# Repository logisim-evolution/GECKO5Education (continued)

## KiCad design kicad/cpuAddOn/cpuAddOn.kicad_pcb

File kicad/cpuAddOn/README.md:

# GECKO5Education CPU-addon

This design can be used with the GECKO5Education or standalone and provides
an educational base for programming related classes.
In case this board is used with the GECKO5Education, the FTDI-chip is automatically
routed to the integrated USB-hub, meaning that you only require one USB-C connection. 
In case of this situation, the USB-C connector of the GECKO5Education is disabled, and all
functionality is provided by the USB-C connector of the CPU-addon board.

# Debugging

This board integrates a [Black Magic Probe](https://black-magic.org/index.html). After production
it needs to be programmed with the DFU-firmware once by an external programmer. After this firmware-
updates can be performed as with the normal Black Magic Probe.

# External connections

This boards integrates an extention connector (32 positions) that provides two 
[PMOD-compatible](https://digilent.com/reference/_media/reference/pmod/pmod-interface-specification-1_2_0.pdf)
interfaces. The different possibilities are listed below:

PMOD1:

|Pin|function1|function2|function3|
|:-:|:--------|:--------|:--------|
|1  |GPIO     |SPI6nCS  |I2S1_WS  |
|2  |GPIO     |SPI6MOSI |I2S1_SDO |
|3  |GPIO     |SPI6MISO |I2S1_SDI |
|4  |GPIO     |SPI6SCK  |I2S1_CK  |
|7  |GPIO     |EXTI5    |         |
|8  |GPIO     |EXTI6    |         |
|9  |GPIO     |SCL4     |         |
|10 |GPIO     |SDA4     |         |

PMOD2:

|Pin|function1|function2|function3|
|:-:|:--------|:--------|:--------|
|1  |GPIO     |CTS2     |         |
|2  |GPIO     |TX2      |         |
|3  |GPIO     |RX2      |         |
|4  |GPIO     |RTS2     |         |
|7  |GPIO     |EXTI13   |         |
|8  |GPIO     |ADC1_2_3 |EXTI0    |
|9  |GPIO     |ADC1_2_3 |EXTI1    |
|10 |GPIO     |ADC3     |EXTI10   |

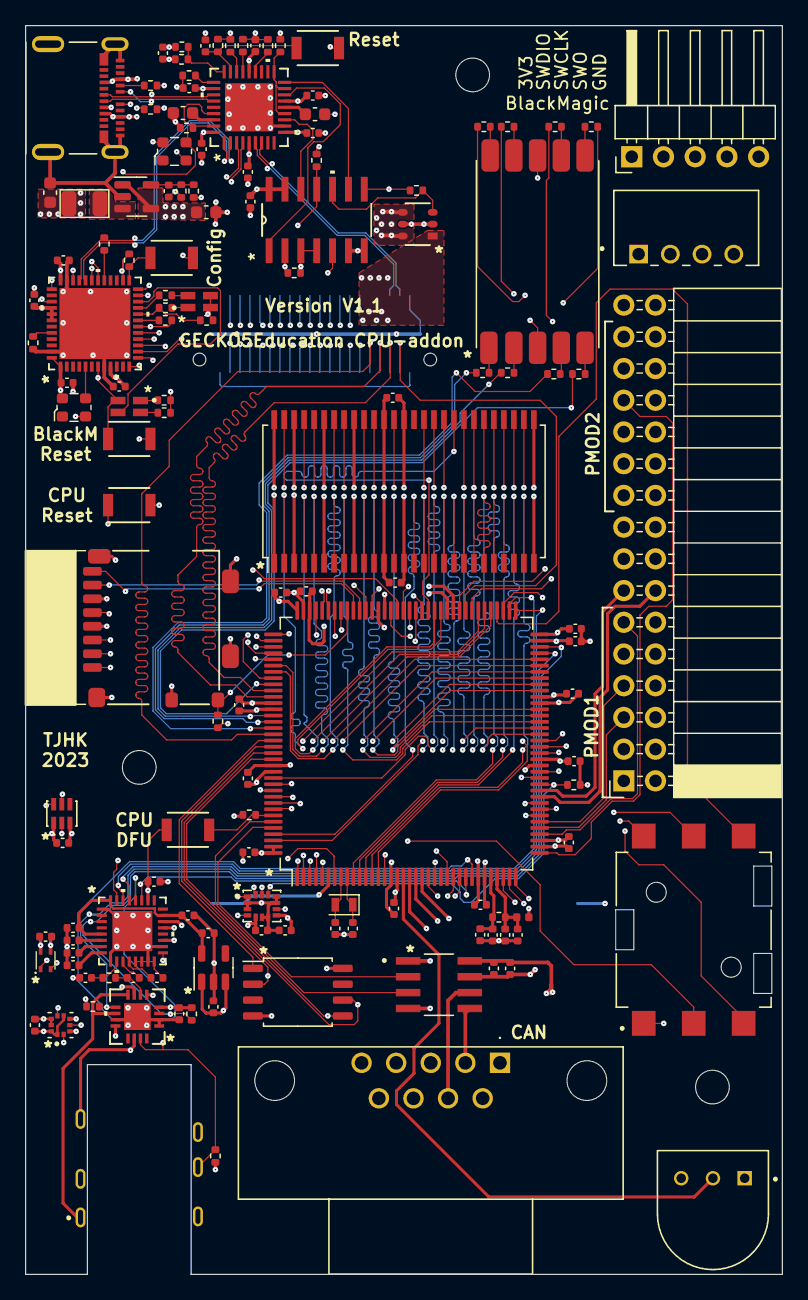
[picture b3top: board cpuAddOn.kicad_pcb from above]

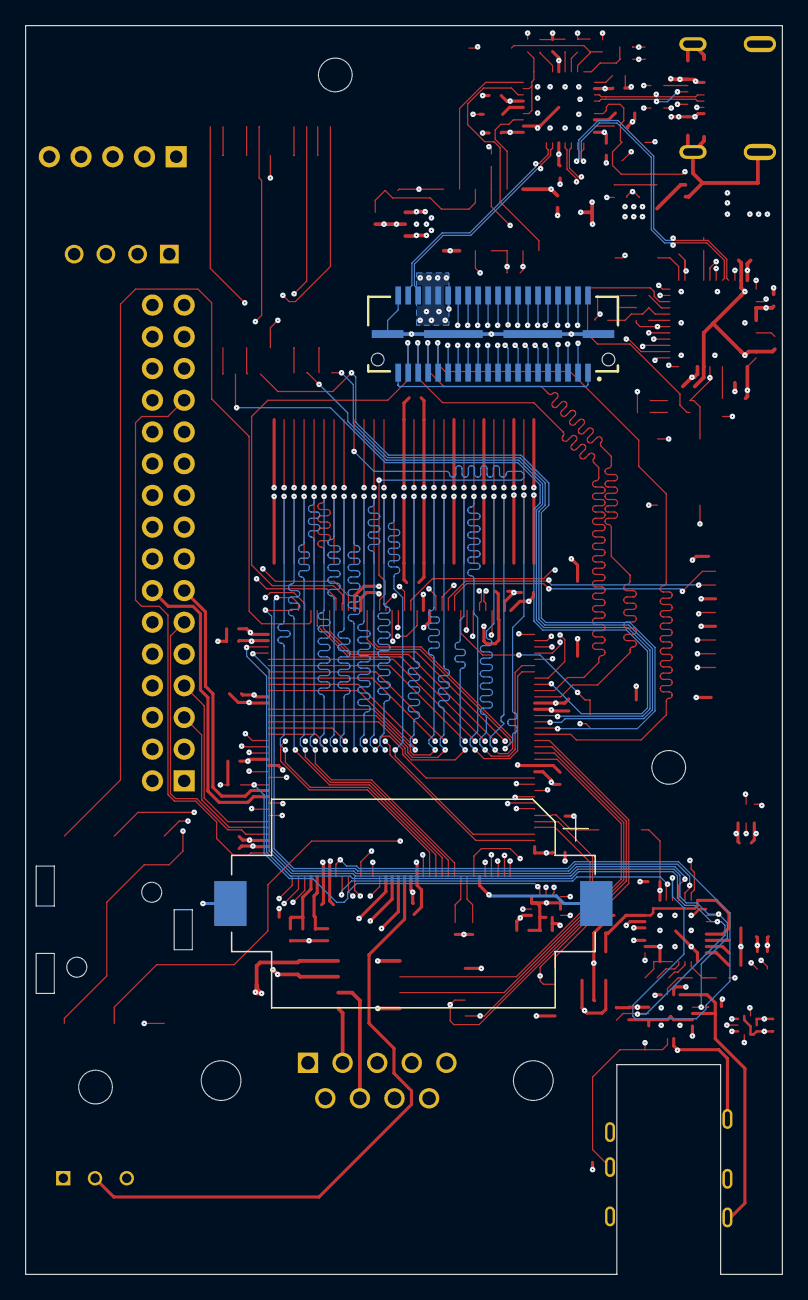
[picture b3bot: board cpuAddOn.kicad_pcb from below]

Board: 6 copper layers, 60.6 x 100.0 mm, 138 parts (2 on the bottom side), 191 nets.

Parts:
A1: LPS22HBTR; PQFN50P200X200X80-10N
BT1: Battery_Cell; BatteryHolder_Keystone_1060_1x2032
C1, C3, C4, C5: C1608X5R0J106M080AB; C_0603_1608Metric
C2: 18p; C_0402_1005Metric
C6, C7, C8, C9, C10, C11, C12, C13, C14, C15, C16, C17, C18, C19, C20, C22, C33, C34, C35, C37, C38, C39, C42, C43, C44, C45, C46, C47, C48, C49, C50, C51, C52, C55: 100n; C_0402_1005Metric
C21, C23, C24, C25, C26, C29, C30, C32, C36, C53, C54: 1u; C_0402_1005Metric
C27, C28: 220n; C_0402_1005Metric
C31, C40, C41: 2u2; C_0402_1005Metric
C56, C57: 9pF; C_0402_1005Metric
D1, D2: APHBM2012SURKCGKC; LED_APHBM2012SURKCGKC
J1: QTE-020-01-X-D-A; SAMTEC_QTE-020-01-X-D-A
J2: 105450-0101; MOLEX_105450-0101
J3: Conn_01x05_Pin; PinHeader_1x05_P2.54mm_Horizontal
J4: SJ-3551B-MSMT-TR-67; CUI_SJ-3551B-MSMT-TR-67
J5: TE_2311765-1
J7: Conn_02x16_Odd_Even; PinSocket_2x16_P2.54mm_Horizontal
L1: LQM2HPN2R2MJ0L
L2: 1k @ 100MHz; L_0402_1005Metric
PS1: B0505S-1WR3; CONV_B0505S-1WR2
R1, R2: 5k1; R_0402_1005Metric
R3, R4, R7: 100k; R_0402_1005Metric
R5: 680k; R_0402_1005Metric
R6: 150k; R_0402_1005Metric
R8: 12k; R_0402_1005Metric
R9, R10, R11, R12, R13, R15, R16, R17, R18, R21, R24, R25, R26, R28, R30, R31, R32, R33: 10k; R_0402_1005Metric
R14: 1k5; R_0402_1005Metric
R19, R22: 768R; R_0402_1005Metric
R20, R23: 330R; R_0402_1005Metric
R27: 3352T-1-103LF; TRIM_3352T-1-103LF
R29: 2k2; R_0402_1005Metric
R34: 47E; R_0402_1005Metric
R35, R36, R37, R38, R39, R40, R41, R42: 62R; R_0402_1005Metric
S1: JS5208
SD1: 104031-0811; sdcard
SW1, SW2, SW3, SW4, SW5: B3U-1000P[]; SW_B3U-1000P_OMR
U1: USB2513B-AEZC; QFN36_6X6MC_MCH
U2: NCP1529A; SOT-23-5
U3: STM32F103CBU6; UFQFPN-48_7X7X0P55MM
U4: SN74HC266DR; D14
U5: AP2281-3WG-7; SOT26_DIO
U6: STM32H743ZITx; LQFP-144_20x20mm_P0.5mm
U7: AS4C16M16SA-6TAN; TSOP-II-54_22.2x10.16mm_P0.8mm
U8: ISO1044BD; SOIC127P599X175-8N
U9: TS3A227ERVAR; RVA16_2P14X2P14_TEX
U10: MAX9867ETJ+; 21-0140L_T3255-4_MXM
U11: LP5907MFX-1.8; SOT-23-5
U12: MX25R3235FM2IL0; SOP-8_5.28x5.23mm_P1.27mm
U13: ICM-42605; PQFN50P300X250X97-14N
U14: SHT40-AD1B-R2; SHT4X
U15: TCS34003FNM; SON65P200X240X70-6N
U16: HDSM-433C; HDSM-431W
X1: ECS-2520MV-240-BL-TR; Oscillator_SMD_ECS_2520MV-xxx-xx-4Pin_2.5x2.0mm
X2: ECS-2520MV-080-BM-TR; Oscillator_SMD_ECS_2520MV-xxx-xx-4Pin_2.5x2.0mm
Y1: RT2012-32.768-9-20-EXT-TR; Crystal_SMD_2012-2Pin_2.0x1.2mm

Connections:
+1V8: C24.1, C32.1, C34.1, U10.5 (AVDD), U10.23 (PVDD), U10.32 (DVDD), U11.5 (OUT)
+3.3V: A1.1 (VDD_IO), A1.6 (CS), A1.10 (VDD), C2.1, C3.1, C8.1, C9.1, C10.1, C11.1, C12.1, C13.1, C14.1, C15.1, C16.1, C17.1, C18.1, C19.1, C20.1, C23.1, C25.1, C33.1, C35.1, C36.1, C37.1, C38.1, C39.1, C42.1, C43.1, C44.1, C45.1, C46.1, C47.1, C48.1, C49.1, C50.1, C51.1, J3.1, J7.1, J7.2, J7.19, J7.20, L1.2, L2.2, R5.1, R7.2, R10.1, R13.2, R15.2, R16.1, R17.1, R22.1, R23.1, R24.1, R25.2, R26.1, R27.3, R28.1, R30.1, R31.2, SD1.4 (VCC), SW5.2, U1.5 (VDDA33), U1.10 (VDDA33), U1.15 (VDD33), U1.23 (VDD33), U1.29 (VDDA33), U1.36 (VDD33), U3.1 (VBAT), U3.9 (VCCA), U3.18 (PB0), U3.24 (VCCB), U3.26 (PB13), U3.36 (VCCC), U3.40 (PB4), U3.41 (PB5), U3.42 (PB6), U3.48 (VCCD), U4.2 (1B), U4.8 (3A), U4.13 (4B), U4.14 (VCC), U6.17 (VDD), U6.30 (VDD), U6.39 (VDD), U6.52 (VDD), U6.62 (VDD), U6.72 (VDD), U6.84 (VDD), U6.95 (VDD33_USB), U6.108 (VDD), U6.121 (VDD), U6.131 (VDD), U6.143 (PDR_ON), U6.144 (VDD), U7.1 (VDD), U7.3 (VDDQ), U7.9 (VDDQ), U7.14 (VDD), U7.27 (VDD), U7.43 (VDDQ), U7.49 (VDDQ), U8.1 (VCC1), U9.4 (VDD), U10.26 (DVDDIO), U11.1 (IN), U11.3 (EN), U12.8 (VCC), U13.5 (VDDIO), U13.8 (VDD), U14.3 (VDD), U15.1 (VDD), X1.4 (VDD), X2.4 (VDD)
+5V: C1.1, C6.1, J2.A4 (VBUS1), J2.A9 (VBUS2), J2.B4 (VBUS3), J2.B9 (VBUS4), PS1.2 (VIN), R4.2, U2.1 (EN), U2.4 (VIN), U5.4 (IN), U5.6 (IN)
/BlackMagicProbe/SWCLK: J3.3, U3.37 (SWCLK)
/BlackMagicProbe/SWDIO: J3.2, U3.34 (SWIO)
/BlackMagicProbe/SWO: J3.4, U3.39 (PB3)
ADC4: J7.17, U6.19 (PF7)
ADC_PWM0: J7.14, U6.46 (PB0)
ADC_PWM1: J7.13, U6.47 (PB1)
ADC_PWM2: J7.16, U6.20 (PF8)
ADC_PWM3: J7.15, U6.21 (PF9)
BlackCpuReset: U3.12 (PA2), U4.5 (2A)
BlackD+: R14.1, U1.2 (USBDP_DN1/PRT_DIS_P1), U3.33 (PA12)
BlackD-: U1.1 (USBDM_DN1/PRT_DIS_M1), U3.32 (PA11)
BlackRxd: U3.30 (PA9), U6.102 (PA10)
BlackTxd: U3.31 (PA10), U6.101 (PA9)
BlacknReset: D2.2, R16.2, SW2.1, U3.7 (NRST), U4.11 (4Y)
BlacknResetDrive: U1.12 (PRTPWR1/BC_EN1), U4.12 (4A)
CPUnReset: R15.1, SW4.1, U3.17 (PA7), U4.3 (1Y), U4.4 (2Y), U6.25 (NRST)
CPUnResetDrive: U1.16 (PRTPWR2/BC_EN2), U4.1 (1A)
CanRxd: U6.139 (PB8), U8.3 (Rxd)
CanTxd: U6.140 (PB9), U8.2 (TxD)
Clock24MHz: U1.33 (XTALIN/CLKIN), U6.23 (PH0), U10.31 (MCLK), X1.3 (OUT)
CodecBclk: U6.74 (PB13), U10.30 (BCLK)
CodecLRclk: U6.73 (PB12), U10.29 (LRCLK)
CodecSDin: U6.29 (PC3_C), U10.28 (SDIN)
CodecSDout: U6.28 (PC2_C), U10.27 (SDOUT)
Color_Int: U6.92 (PG7), U15.5 (INT)
CpuD+: U1.4 (USBDP_DN2/PRT_DIS_P2), U6.104 (PA12)
CpuD-: U1.3 (USBDM_DN2/PRT_DIS_M2), U6.103 (PA11)
CpuTckSwclk: U3.15 (PA5), U6.109 (PA14)
CpuTdi: U3.13 (PA3), U6.110 (PA15)
CpuTdoSwo: U3.16 (PA6), U6.133 (PB3)
CpuTmsSwdio: U3.14 (PA4), U6.105 (PA13)
D1+: J2.A6 (D1+), J2.B6 (D2+), U1.31 (USBDP_UP)
D1-: J2.A7 (D1-), J2.B7 (D2-), U1.30 (USBDM_UP)
EnFPGA: R17.2, U4.10 (3Y), U5.3 (EN)
FMC_A0: J1.24, U6.10 (PF0), U7.23 (A0)
FMC_A1: J1.26, U6.11 (PF1), U7.24 (A1)
FMC_A2: J1.28, U6.12 (PF2), U7.25 (A2)
FMC_A3: J1.30, U6.13 (PF3), U7.26 (A3)
FMC_A4: J1.29, U6.14 (PF4), U7.29 (A4)
FMC_A5: J1.27, U6.15 (PF5), U7.30 (A5)
FMC_A6: J1.25, U6.50 (PF12), U7.31 (A6)
FMC_A7: J1.23, U6.53 (PF13), U7.32 (A7)
FMC_A8: J1.21, U6.54 (PF14), U7.33 (A8)
FMC_A9: J1.20, U6.55 (PF15), U7.34 (A9)
FMC_A10: J1.22, U6.56 (PG0), U7.22 (A10/AP)
FMC_A11: J1.19, U6.57 (PG1), U7.35 (A11)
FMC_A12: U6.87 (PG2), U7.36 (A12)
FMC_BA0: U6.89 (PG4), U7.20 (BA0)
FMC_BA1: U6.90 (PG5), U7.21 (BA1)
FMC_CKE: U6.45 (PC5), U7.37 (CKE)
FMC_CLK: U6.93 (PG8), U7.38 (CLK)
FMC_D0: J1.03, U6.85 (PD14), U7.2 (DQ0)
FMC_D1: J1.05, U6.86 (PD15), U7.4 (DQ1)
FMC_D2: J1.07, U6.114 (PD0), U7.5 (DQ2)
FMC_D3: J1.09, U6.115 (PD1), U7.7 (DQ3)
FMC_D4: J1.11, U6.58 (PE7), U7.8 (DQ4)
FMC_D5: J1.13, U6.59 (PE8), U7.10 (DQ5)
FMC_D6: J1.15, U6.60 (PE9), U7.11 (DQ6)
FMC_D7: J1.17, U6.63 (PE10), U7.13 (DQ7)
FMC_D8: J1.18, U6.64 (PE11), U7.42 (DQ8)
FMC_D9: J1.16, U6.65 (PE12), U7.44 (DQ9)
FMC_D10: J1.14, U6.66 (PE13), U7.45 (DQ10)
FMC_D11: J1.12, U6.67 (PE14), U7.47 (DQ11)
FMC_D12: J1.10, U6.68 (PE15), U7.48 (DQ12)
FMC_D13: J1.08, U6.77 (PD8), U7.50 (DQ13)
FMC_D14: J1.06, U6.78 (PD9), U7.51 (DQ14)
FMC_D15: J1.04, U6.79 (PD10), U7.53 (DQ15)
FMC_DQM0: U6.141 (PE0), U7.15 (LDQM)
FMC_DQM1: U6.142 (PE1), U7.39 (UDQM)
FMC_nCAS: U6.132 (PG15), U7.17 (~CAS)
FMC_nCS: U6.44 (PC4), U7.19 (~CS)
FMC_nRAS: U6.49 (PF11), U7.18 (~RAS)
FMC_nWE: U6.43 (PA7), U7.16 (~WE)
FPGADrive: U1.18 (PRTPWR3/BC_EN3), U4.9 (3B)
FPGA_IRQ: J1.37, U6.81 (PD12)
FPGA_nCS: J1.31, U6.125 (PG10)
FPGA_nOE: J1.35, U6.118 (PD4)
FPGA_nWE: J1.33, U6.119 (PD5)
GND: A1.3 (RESERVED), A1.5 (SDO/SA0), A1.8 (GND), A1.9 (GND), BT1.2 (-), C1.2, C3.2, C4.2, C5.2, C6.2, C7.2, C8.2, C9.2, C10.2, C11.2, C12.2, C13.2, C14.2, C15.2, C16.2, C17.2, C18.2, C19.2, C20.2, C23.2, C24.2, C25.2, C26.1, C28.2, C29.2, C30.2, C31.2, C32.2, C33.2, C34.2, C35.2, C36.2, C37.2, C38.2, C39.2, C40.2, C41.2, C42.2, C43.2, C44.2, C45.2, C46.2, C47.2, C48.2, C49.2, C50.2, C51.2, C52.2, C53.2, C54.2, C55.2, C56.2, C57.2, D1.2, D1.3, J1.40, J1.G1 (GND), J1.G2 (GND), J1.G3 (GND), J1.G4 (GND), J2.A1 (GND1), J2.A12 (GND2), J2.B1 (GND3), J2.B12 (GND4), J2.S1 (SHIELD), J2.S2 (SHIELD), J2.S3 (SHIELD), J2.S4 (SHIELD), J3.5, J4.6, J7.3, J7.4, J7.18, J7.21, J7.22, J7.31, PS1.1 (GND), R1.1, R2.1, R3.1, R6.2, R8.1, R9.1, R11.1, R12.1, R18.1, R21.1, R27.1, R32.2, R33.1, S1.1, SD1.6 (GND), SD1.GM1 (GND), SD1.GM2 (GND), SD1.GM3 (GND), SD1.GM4 (GND), SD1.GS4 (GND), SW1.2, SW2.2, SW3.2, SW4.2, U1.11 (TEST), U1.37 (EPAD), U2.2 (GND), U3.8 (GNDA), U3.23 (GNDB), U3.35 (GNDC), U3.47 (GNDD), U3.49 (EPAD), U4.6 (2B), U4.7 (GND), U5.2 (GND), U5.5 (GND), U6.16 (VSS), U6.31 (VSSA), U6.38 (VSS), U6.51 (VSS), U6.61 (VSS), U6.83 (VSS), U6.94 (VSS), U6.107 (VSS), U6.120 (VSS), U6.130 (VSS), U7.6 (VSSQ), U7.12 (VSSQ), U7.28 (VSS), U7.41 (VSS), U7.46 (VSSQ), U7.52 (VSSQ), U7.54 (VSS), U8.4 (GND1), U9.1 (GND), U9.2 (GND), U9.11 (GNDA), U9.17 (EPAD), U10.1 (DGND), U10.9 (AGND), U10.13 (MICRP), U10.14 (MICRN), U10.15 (LINL), U10.16 (LINR), U10.18 (PGND), U10.33 (EPAD), U11.2 (GND), U12.4 (GND), U13.2 (RESV_1), U13.3 (RESV_2), U13.6 (GND), U13.7 (RESV_3), U13.10 (RESV_4), U13.11 (RESV_5), U14.4 (VSS), U15.3 (GND), U16.3 (CC), U16.8 (CC), X1.2 (GND), X2.2 (GND)
Joy2: S1.2, U6.134 (PB4)
Joy3: S1.3, U6.1 (PE2)
Joy4: S1.4, U6.2 (PE3)
Joy5: S1.5, U6.3 (PE4)
Joy6: S1.6, U6.76 (PB15)
Motion_Int1: U6.88 (PG3), U13.4 (INT1/INT)
Motion_Int2: U6.75 (PB14), U13.9 (INT2/FSYNC)
Motion_nCS: R32.1, U6.48 (PB2), U13.12 (AP_CS)
unnamed: BT1.1 (+), J7.32, U6.6 (VBAT)
unnamed: C40.1, C41.1, U6.71 (VCAP), U6.106 (VCAP)
unnamed: D1.1, R19.1
unnamed: D1.4, R20.1
unnamed: D2.1, R22.2
unnamed: D2.4, R23.2
unnamed: J1.01, J1.39
unnamed: J2.A5 (CC1), R1.2
unnamed: J2.B5 (CC2), R2.2
unnamed: C21.2, C22.2, PS1.3 (0V), U8.7 (GND2)
unnamed: C21.1, C22.1, PS1.4 (+VO), U8.8 (VCC2)
unnamed: C5.1, U1.14 (CRFILT)
unnamed: R10.2, U1.25 (HS_IND/CFG_SEL1)
unnamed: R25.1, U1.13 (OCS_N1), U1.17 (OCS_N2), U1.19 (OCS_N3)
unnamed: C4.1, U1.34 (PLLFILT)
unnamed: R8.2, U1.35 (RBIAS)
unnamed: C7.1, R7.1, SW3.1, U1.26 (RESET_N)
unnamed: R11.2, U1.24 (SCL/SMBCLK/CFG_SEL0)
unnamed: R12.2, U1.22 (SDA/SMBDATA/NON_REM1)
unnamed: R9.2, U1.28 (SUSP_IND/LOCAL_PWR/NON_REM0)
unnamed: R3.2, R4.1, U1.27 (VBUS_DET)
unnamed: C2.2, R5.2, R6.1, U2.5 (FB)
unnamed: L1.1, U2.3 (SW)
unnamed: R18.2, U3.44 (BOOT0)
unnamed: U3.5 (OSCIN), X2.3 (OUT)
unnamed: R14.2, U3.29 (PA8)
unnamed: R13.1, U3.19 (PB1)
unnamed: R19.2, R21.2, U3.20 (PB2/BOOT1)
unnamed: R20.2, U3.21 (PB10)
unnamed: D2.3, U3.22 (PB11)
unnamed: R24.2, SW1.1, U3.25 (PB12)
unnamed: J1.32, J1.34, U5.1 (OUT)
unnamed: R33.2, SW5.1, U6.138 (BOOT0)
unnamed: C56.1, U6.8 (PC14), Y1.2
unnamed: C57.1, U6.9 (PC15), Y1.1
unnamed: R27.2, U6.18 (PF6)
unnamed: C54.1, C55.1, L2.1, R34.1, U6.33 (VDDA)
unnamed: C52.1, C53.1, R34.2, U6.32 (VREF+)
unnamed: J5.7, U8.6 (CANH)
unnamed: J5.2, U8.5 (CANL)
unnamed: C27.1, R29.1, U9.6 (MICP)
unnamed: J4.4, U9.7 (RING2_SENSE), U9.12 (RING2)
unnamed: J4.1, U9.8 (SLEEVE_SENSE), U9.10 (SLEEVE)
unnamed: J4.5, R28.2, U9.15 (*DET_TRIGGER), U10.17 (JACKSNS/AUX)
unnamed: U9.5 (GND_SENSE), U10.21 (LOUTN)
unnamed: J4.2, U9.14 (TIP), U10.22 (LOUTP)
unnamed: C26.2, R29.2, U10.10 (MICBIAS)
unnamed: C27.2, U10.11 (MICLN/DIGMICCLK)
unnamed: C28.1, U10.12 (MICLP/DIGMICDATA)
unnamed: C30.1, U10.7 (PREG)
unnamed: C31.1, U10.6 (REF)
unnamed: C29.1, U10.8 (REG)
unnamed: J4.3, U10.19 (ROUTP)
unnamed: R35.2, U16.7 (A)
unnamed: R36.2, U16.6 (B)
unnamed: R37.2, U16.4 (C)
unnamed: R38.2, U16.2 (D)
unnamed: R42.2, U16.5 (DP)
unnamed: R39.2, U16.1 (E)
unnamed: R40.2, U16.9 (F)
unnamed: R41.2, U16.10 (G)
PMOD1_1: J7.11, U6.40 (PA4)
PMOD1_2: J7.9, U6.135 (PB5)
PMOD1_3: J7.7, U6.42 (PA6)
PMOD1_4: J7.5, U6.41 (PA5)
PMOD1_7: J7.12, U6.4 (PE5)
PMOD1_8: J7.10, U6.5 (PE6)
PMOD1_9: J7.8, U6.136 (PB6)
PMOD1_10: J7.6, U6.137 (PB7)
PMOD2_1: J7.29, U6.34 (PA0)
PMOD2_2: J7.27, U6.36 (PA2)
PMOD2_3: J7.25, U6.37 (PA3)
PMOD2_4: J7.23, U6.35 (PA1)
PMOD2_7: J7.30, U6.7 (PC13)
PMOD2_8: J7.28, U6.27 (PC1)
PMOD2_9: J7.26, U6.26 (PC0)
PMOD2_10: J7.24, U6.22 (PF10)
Presure_Irq: A1.7 (INT_DRDY), U6.91 (PG6)
SCL: A1.2 (SCL/SPC), R31.1, U6.69 (PB10), U9.9 (SCL), U10.2 (SCL), U14.2 (SCL), U15.2 (SCL)
SDA: A1.4 (SDA/SDI/SDO), R30.2, U6.70 (PB11), U9.3 (SDA), U10.3 (SDA), U14.1 (SDA), U15.6 (SDA)
SD_CLK: SD1.5 (CLK), U6.113 (PC12)
SD_CMD: SD1.3 (CMD), U6.116 (PD2)
SD_D0: SD1.7 (DAT0), U6.98 (PC8)
SD_D1: SD1.8 (DAT1), U6.99 (PC9)
SD_D2: SD1.1 (DAT2), U6.111 (PC10)
SD_D3: SD1.2 (CD/DAT3), U6.112 (PC11)
SD_nDET: R26.2, SD1.10 (SW-2), U6.100 (PA8)
Seg_A: R35.1, U6.80 (PD11)
Seg_B: R36.1, U6.82 (PD13)
Seg_C: R37.1, U6.124 (PG9)
Seg_D: R38.1, U6.122 (PD6)
Seg_DP: R42.1, U6.117 (PD3)
Seg_E: R39.1, U6.123 (PD7)
Seg_F: R40.1, U6.97 (PC7)
Seg_G: R41.1, U6.96 (PC6)
USERF_SCLK: U6.128 (PG13), U12.6 (SCLK), U13.13 (AP_SCL/AP_SCLK)
USERF_SI: U6.129 (PG14), U12.5 (SI/SIO0), U13.14 (AP_SDA/AP_SDIO/AP_SDI)
USERF_SO: U6.127 (PG12), U12.2 (SO/SIO1), U13.1 (AP_SDO/AP_ADO)
USERF_nCS: U6.126 (PG11), U12.1 (~CS)
UsbD+: J1.38, U1.7 (USBDP_DN3/PRT_DIS_P3)
UsbD-: J1.36, U1.6 (USBDM_DN3/PRT_DIS_M3)

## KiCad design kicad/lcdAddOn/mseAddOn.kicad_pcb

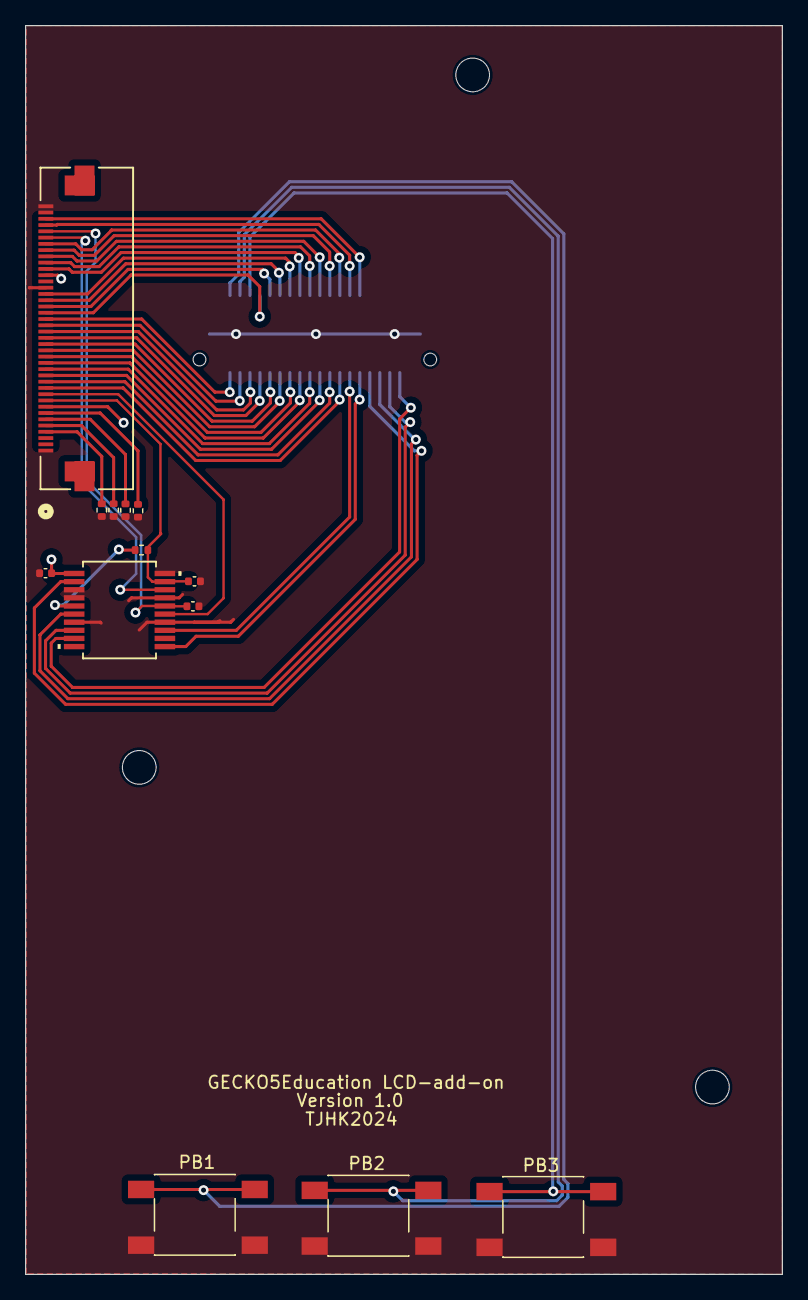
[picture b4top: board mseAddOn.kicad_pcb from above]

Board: 2 copper layers, 60.6 x 100.0 mm, 14 parts (1 on the bottom side), 43 nets.

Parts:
C1, C2: 10pF; C_0402_1005Metric
C3: 100nF; C_0402_1005Metric
J1: QTE-020-01-F-D-A; SAMTEC_QTE-020-01-X-D-A
J2: 62684-402100ALF; CONN_62684-402100ALF_AMP
R1, R2, R3, R4: 2E; R_0402_1005Metric
R5: 20k; R_0402_1005Metric
SW1, SW2, SW3: SW_Push; pushbutton
U1: AR1021-I/SS; SSOP20_MC_MCH

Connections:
+3.3V: C3.1, J1.01, J1.02, J1.39, J2.8, J2.29, U1.1 (VDD)
CS: J1.22, J2.32
DB0: J1.15, J2.16
DB1: J1.17, J2.15
DB2: J1.19, J2.14
DB3: J1.21, J2.13
DB4: J1.23, J2.12
DB5: J1.25, J2.11
DB6: J1.13, J2.17
DB7: J1.11, J2.18
DB8: J1.09, J2.19
DB9: J1.07, J2.20
DB10: J1.05, J2.21
DB11: J1.03, J2.22
DB12: J1.10, J2.23
DB13: J1.12, J2.24
DB14: J1.14, J2.25
DB15: J1.16, J2.26
FMARK: J1.28, J2.37
GND: C1.2, C2.2, C3.2, J1.G1 (GND), J1.G2 (GND), J1.G3 (GND), J1.G4 (GND), J2.1, J2.27, J2.39, J2.40, R1.1, R2.1, R3.1, R4.1, SW1.2, SW2.2, SW3.2, U1.3 (SY-), U1.4 (M2), U1.7 (SY+), U1.14 (SX+), U1.17 (5WSX-), U1.20 (VSS)
IMO: J1.30, J2.38
M1: J1.31, U1.2 (M1)
unnamed: J1.04, SW1.1
unnamed: J1.06, SW2.1
unnamed: J1.08, SW3.1
unnamed: J2.4, R4.2
unnamed: J2.5, R3.2
unnamed: J2.6, R2.2
unnamed: J2.7, R1.2
unnamed: R5.1, U1.5 (WAKE)
RD: J1.20, J2.31
RESET: J1.26, J2.34
RS: J1.24, J2.33
SCK/SCL: J1.29, U1.11 (SCK/SCL/TX)
SDI/SDA: J1.27, U1.13 (SDI/SDA/RX)
SDO: J1.37, U1.9 (SDO)
SIQ: J1.33, U1.6 (SIQ)
SS: J1.35, U1.8 (SS)
WR: J1.18, J2.30
X+: J2.35, U1.18 (X+)
X-: C1.1, J2.9, R5.2, U1.19 (X-)
Y+: J2.10, U1.15 (Y+)
Y-: C2.1, J2.36, U1.16 (Y-)

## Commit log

2023-06-18 Added kicad files
2023-06-18 Added 3D model for the SD-card reader
2023-06-18 Updated the README.md with minimal information
2023-06-18 Removed the nDet from the SD-card and added the 12 MHz oscillator as clock input to be fully compatible with the GECKO4 clock inputs
2023-07-04 Added an USB-switch and mountig holes for better connection of add-on cards. Created a template for add-on cards.
2023-07-19 Added add-on board template. Added a CPU-add-on board.
2023-07-24 Small revision on PCB
2023-07-24 Removed typo
2023-07-24 nother typo
2023-07-24 Removed name
2023-07-24 Updated to english link
2023-07-24 Fixed typo
2023-08-07 fixed bug with RS232 Added support for bigger SDRAMs Changed 7-segment display to SMD and active low
2023-08-10 Made V1.1 of the cpu-addon
2023-08-22 Made an alternative version
2023-09-10 Small modifications plus added documentation
2023-09-27 Made version V1.5
2023-09-29 No change
2023-10-01 Made V1.6
2023-10-18 No changes
2023-10-20 Updated price list
2023-10-20 First version
2023-10-20 Updated diode
2023-11-01 Fixed small bug
2023-11-01 small progress
2023-11-03 Added SII9022
2023-11-03 small update on V1.4
2023-12-07 Added 2 add-on boards and updated GECKO5 to support olimex camera-OV7670 and an RTC.
2023-12-07 Added bom
2024-01-09 lates version
2024-01-09 removed SII9022
2024-01-09 Added chip
2024-01-10 Final version
2024-01-29 latest version with camera
2024-01-29 Test
2024-04-17 V1.1 of perifAddOn (added bus-switch on sd-card)
2024-04-29 Added latest images
2024-05-07 Merged perif-add-on to GECKO5
2024-05-22 Prototype Version V3.0
2024-05-22 Changed the USB-reset to reset the FPGA to reconfigure instead of applying the "reset" button, which makes more sense in a system reset
2024-05-22 Updated bom for Discovery II/III connector
2024-06-12 Moved reset to ninit of FPGA, which makes more sense
2024-07-10 Production version EPFL
2024-07-10 Cleaned up
2024-07-10 removed obsolete SII164 and replaced by TFP410
2024-11-11 Added faster AD-converter. Changed "System Reset" into "Board Reset"
2025-03-22 Updated shape
2025-03-22 Switched to less expensive RGB-Leds
2025-07-10 Put faster ADC
2025-07-16 Added developer's guide
2025-07-16 resized image
2025-07-16 Added developper's guide
